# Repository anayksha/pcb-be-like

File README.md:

# pcb-be-like
So this is a really sketchy h-bridge circuit that is capable of running the vibration motor in 2 different directions with 2 different button presses. Yeah, it's kind of useless when it's hooked up to a vibration motor and not an actual motor, but like I wanted to mess around with transistors and I lowk didn't know what else I could make that wasn't too simple nor too complex for me. 

## Schematic

## PCB
I hid the silkscreens over here because it got really cluttered but the silksceens are on the next images<br>
<br><br>

Since the least amount of pcbs I can buy is 5, I wanted to do something with the extras, and so I thought of making the back silkscreen layer some kind of dog tags of Jorge from halo reach.<br>

## BOM
* 1x battery holder
* 2x push buttons
* 4x 4.7kΩ resistors
* 2x 47kΩ resistors
* 4x NPN transistors
* 2x PNP transistors
* 1x 10μF capacitor
* 1x potentiometer
* 1x vibration motor

made by `@anaykshatriya` on slack

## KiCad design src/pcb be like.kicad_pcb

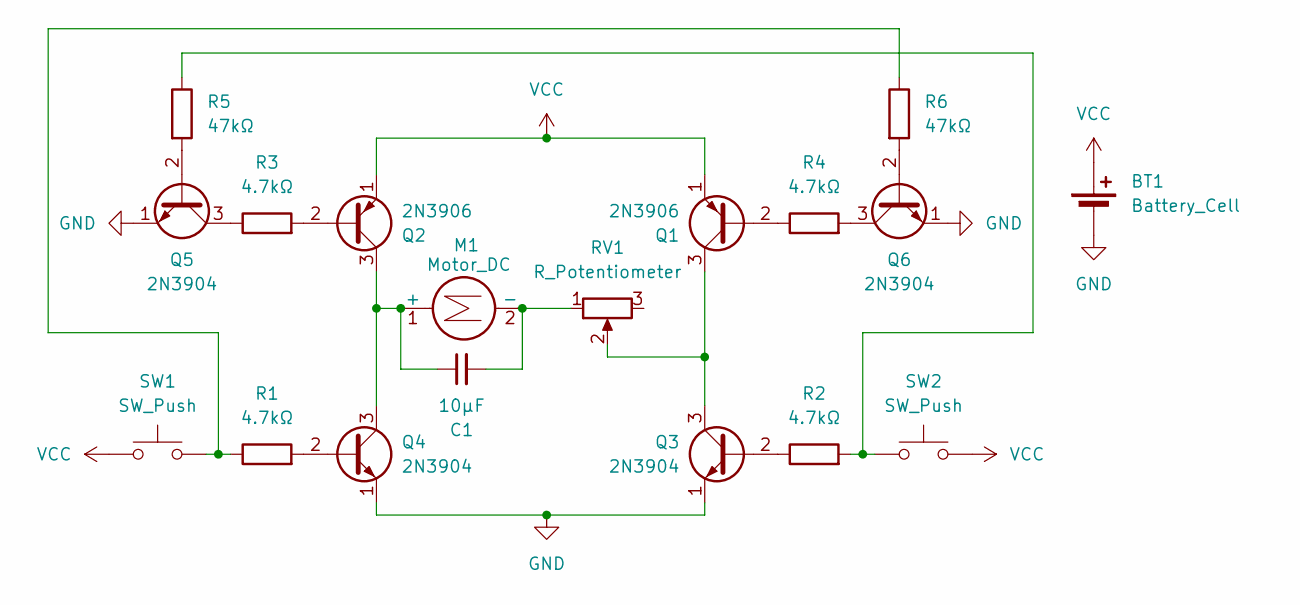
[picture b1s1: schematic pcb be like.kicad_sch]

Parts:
BT1: Battery_Cell; BatteryHolder_Keystone_3034_1x20mm
C1: 10μF; CP_Radial_D8.0mm_P5.00mm
M1: Motor_DC; PinHeader_1x02_P2.54mm_Vertical
Q1, Q2: 2N3906; TO-92L_HandSolder
Q3, Q4, Q5, Q6: 2N3904; TO-92L_HandSolder
R1, R2, R3, R4: 4.7kΩ; R_Axial_DIN0207_L6.3mm_D2.5mm_P7.62mm_Horizontal
R5, R6: 47kΩ; R_Axial_DIN0207_L6.3mm_D2.5mm_P7.62mm_Horizontal
RV1: R_Potentiometer; Potentiometer_Vishay_T73YP_Vertical
SW1, SW2: SW_Push; SW_PUSH_6mm_H5mm

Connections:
GND: BT1.2 (-), Q3.1 (E), Q4.1 (E), Q5.1 (E), Q6.1 (E)
unnamed: C1.1, M1.1 (+), Q2.3 (C), Q4.3 (C)
unnamed: C1.2, M1.2 (-), RV1.1
unnamed: Q1.2 (B), R4.1
unnamed: Q1.3 (C), Q3.3 (C), RV1.2
unnamed: Q2.2 (B), R3.2
unnamed: Q3.2 (B), R2.1
unnamed: Q4.2 (B), R1.2
unnamed: Q5.2 (B), R5.2
unnamed: Q5.3 (C), R3.1
unnamed: Q6.2 (B), R6.2
unnamed: Q6.3 (C), R4.2
unnamed: R1.1, R6.1, SW1.2
unnamed: R2.2, R5.1, SW2.1
VCC: BT1.1 (+), Q1.1 (E), Q2.1 (E), SW1.1, SW2.2

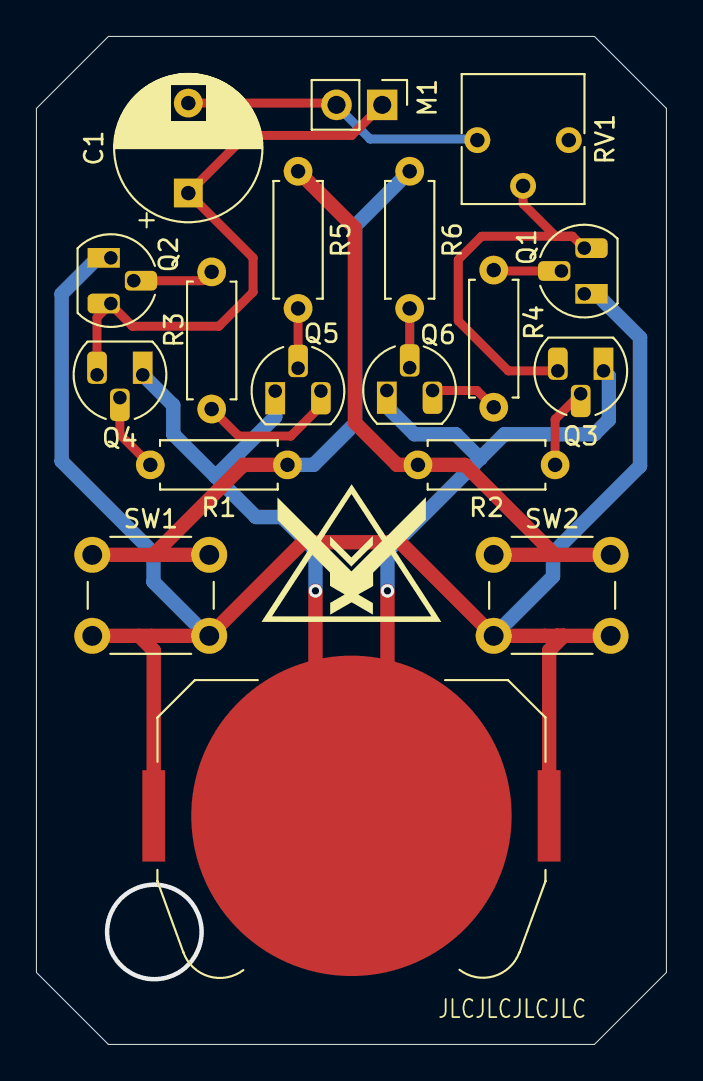
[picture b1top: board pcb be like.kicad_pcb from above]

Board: 2 copper layers, 35.0 x 56.0 mm, 18 parts (0 on the bottom side), 15 nets.

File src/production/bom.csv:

Designator,Footprint,Quantity,Value,LCSC Part #
BT1,BatteryHolder_Keystone_3034_1x20mm,1,Battery_Cell,
C1,CP_Radial_D8.0mm_P5.00mm,1,10μF,
M1,PinHeader_1x02_P2.54mm_Vertical,1,Motor_DC,
"Q1, Q2",TO-92L_HandSolder,2,2N3906,
"Q3, Q4, Q5, Q6",TO-92L_HandSolder,4,2N3904,
"R1, R2, R3, R4",R_Axial_DIN0207_L6.3mm_D2.5mm_P7.62mm_Horizontal,4,4.7kΩ,
"R5, R6",R_Axial_DIN0207_L6.3mm_D2.5mm_P7.62mm_Horizontal,2,47kΩ,
RV1,Potentiometer_Vishay_T73YP_Vertical,1,R_Potentiometer,
"SW1, SW2",SW_PUSH_6mm_H5mm,2,SW_Push,

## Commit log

2025-05-09 created repo
2025-05-09 edited README a little
2025-05-09 added images
2025-05-09 updated README.md and images
2025-05-09 kinda fixed README.md
2025-05-09 fixed README.md again 💀
2025-05-09 forgot slack username for README.md
2025-05-15 final?
2025-05-15 final
2025-05-16 final final (sent for manufacturing)
